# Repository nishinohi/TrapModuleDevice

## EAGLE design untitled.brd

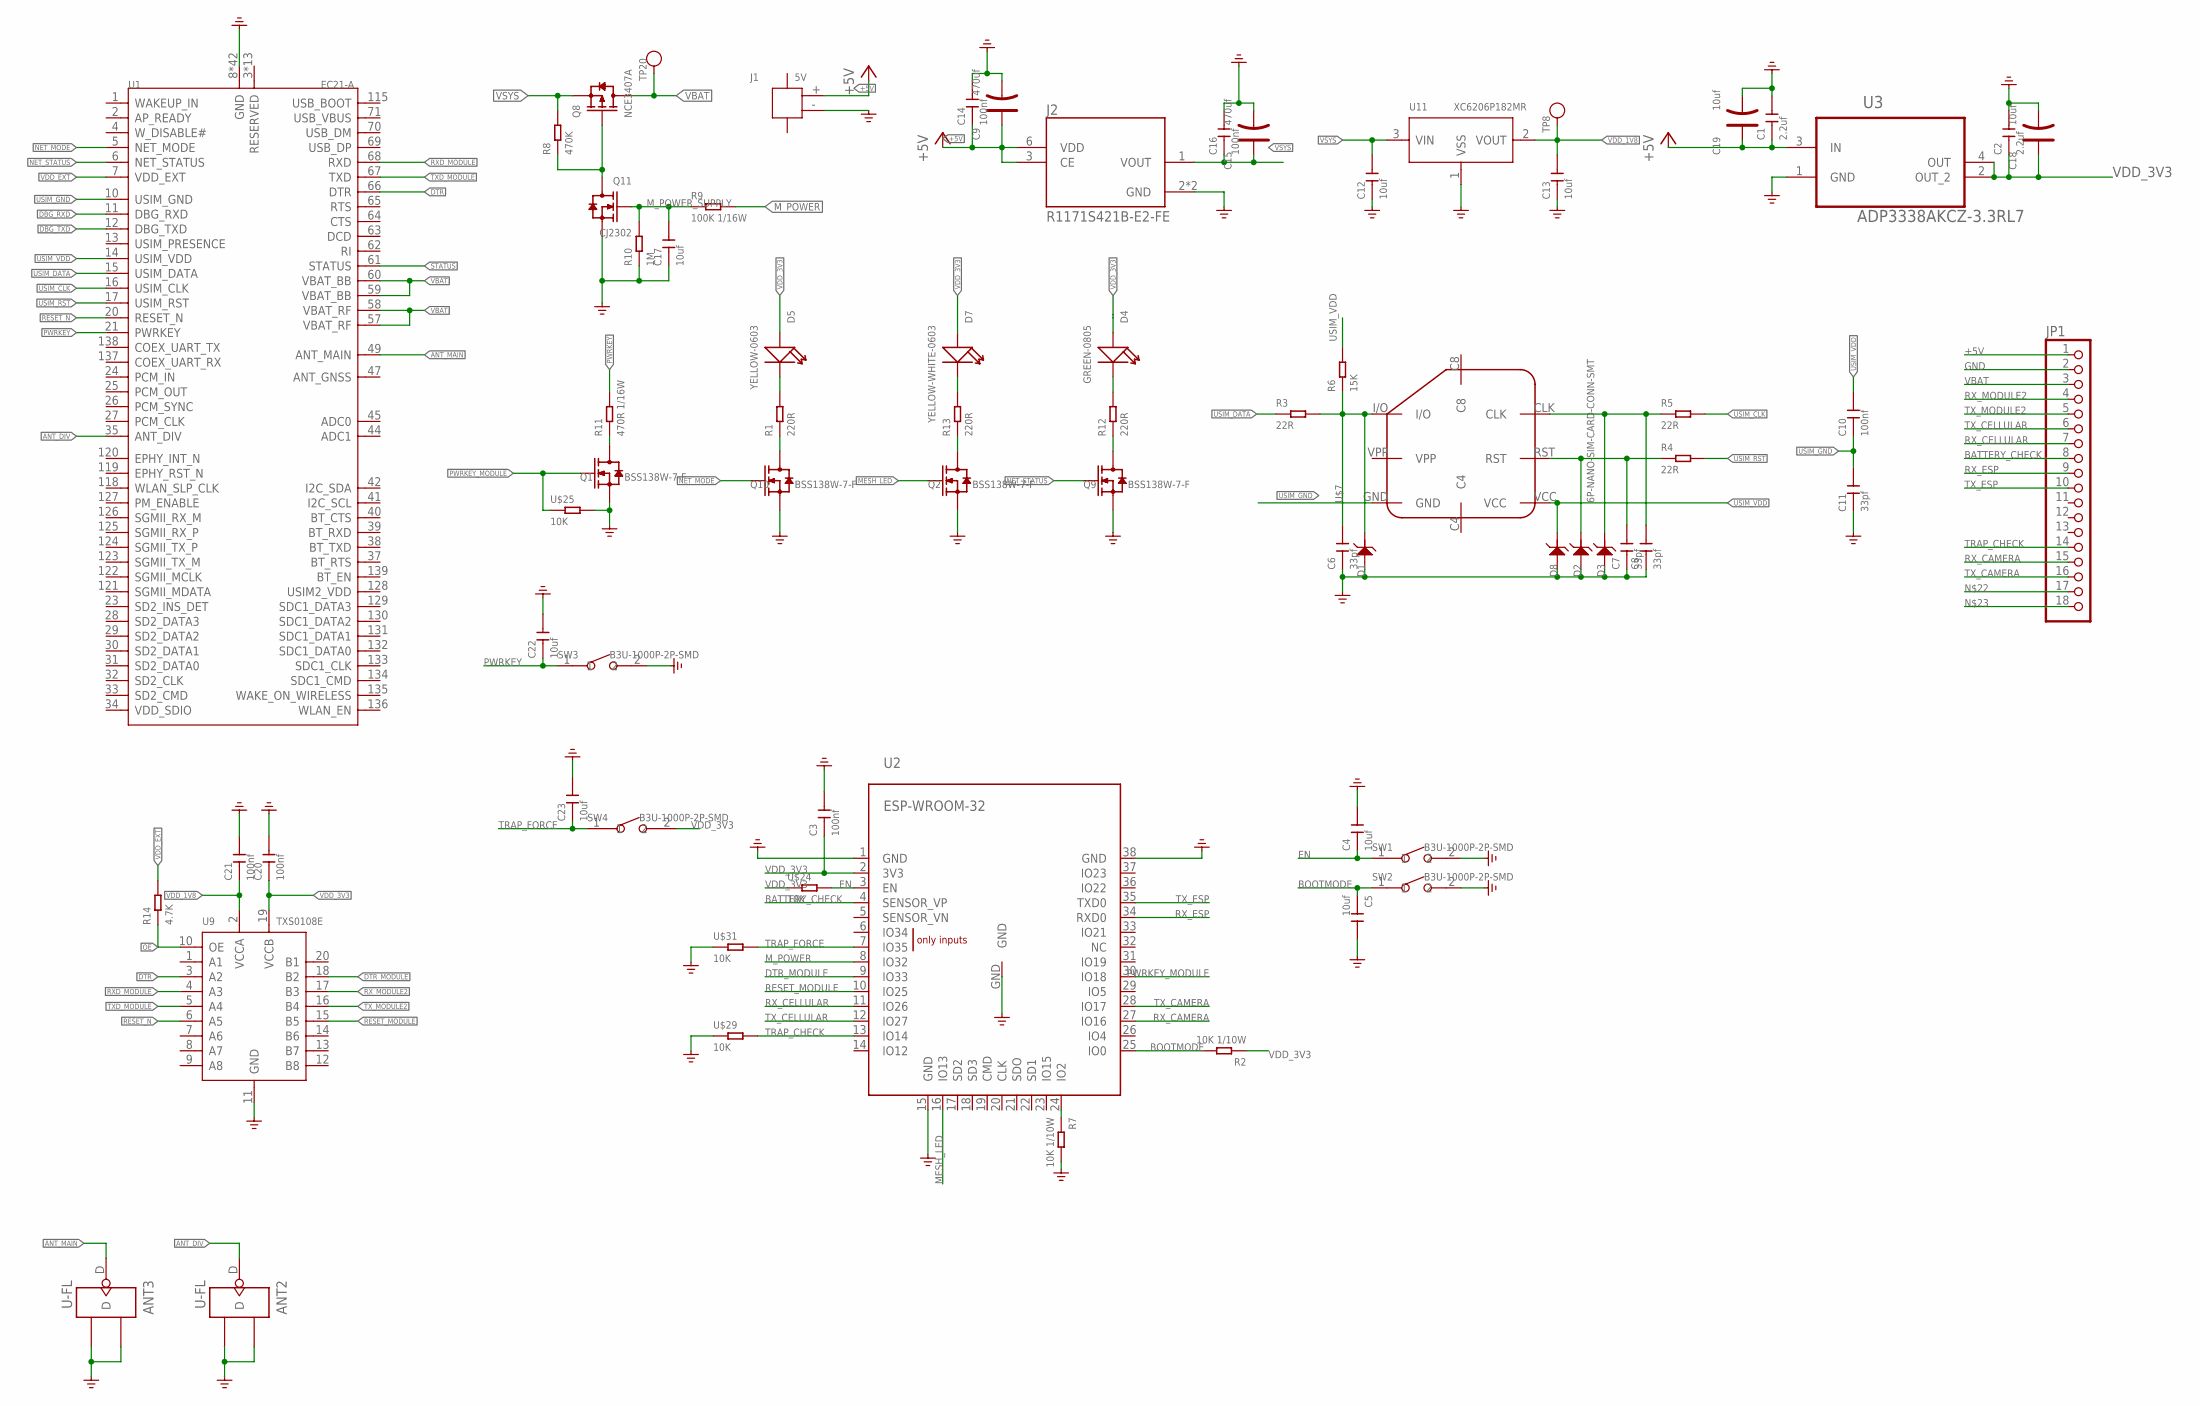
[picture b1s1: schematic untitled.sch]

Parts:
ANT2, ANT3: U-FL; U-FL3P-SMD-2.6X2.6X1.0MM
C1, C2: 2.2uf; C0603
C3, C10, C14, C16, C20, C21: 100nf; C0402
C4, C5, C12, C13, C22, C23: 10uf; C0603
C6, C7, C8, C11: 33pf; C0402
C9, C15: 470uf; AVX-D
C17: 10uf; C0402
C18, C19: 10uf; AVX-A
D1, D2, D3, D8: ESD;DF2S6.8FS; SOD-923
D4: GREEN-0805; LED-0805
D5: YELLOW-0603; LED-0603
D7: YELLOW-WHITE-0603; LED-0603
J1: 5V; HW2-SMD-2.0-90D
J2: R1171S421B-E2-FE; REG_R1171S421B-E2-FE
JP1: HEADER-1X18; 1X18_ROUND70
Q1, Q2, Q9, Q10: BSS138W-7-F; SOT-23
Q8: NCE3407A; SOT-23
Q11: CJ2302; SOT-23
R1, R12, R13: 220R; R0603
R2, R7: 10K 1/10W; R0603
R3, R4, R5: 22R; R0603
R6: 15K; R0603
R8: 470K; R0402
R9: 100K 1/16W; R0402
R10: 1M; R0402
R11: 470R 1/16W; R0402
R14: 4.7K; R0402
SW1, SW2, SW3, SW4: B3U-1000P-2P-SMD; SW2-2.6-3.0X2.5X1.2+0.4MM
TP8, TP20: TEST-POINT'4545'; TP-D45MIL
U1: EC21-A; MODULE144P-1.3-32X29X2.4MM
U2: ESP-WROOM-32
U3: ADP3338AKCZ-3.3RL7; SOT230P700X180-4N
U9: TXS0108E; TSSOP20-0.65-6.5X4.4MM
U11: XC6206P182MR; SOT-23
U$7: 6P-NANO-SIM-CARD-CONN-SMT; 6PIN-NANO-SIM-SMT
U$24, U$25, U$29, U$31: 10K; R0402

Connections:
+5V: C1.1, C9.+, C14.1, C19.+, J1.+ (1), J2.3 (CE), J2.6 (VDD), JP1.1, U3.3 (IN)
ANT_DIV: ANT2.D, U1.35 (ANT_DIV)
ANT_MAIN: ANT3.D, U1.49 (ANT_MAIN)
BATTERY_CHECK: JP1.8, U2.4 (SENSOR_VP)
BOOTMODE: C5.1, R2.2, SW2.1, U2.25 (IO0)
DBG_RXD: U1.11 (DBG_RXD)
DBG_TXD: U1.12 (DBG_TXD)
DTR: U1.66 (DTR), U9.3 (A2)
DTR_MODULE: U2.9 (IO33), U9.18 (B2)
EN: C4.1, SW1.1, U2.3 (EN), U$24.2
GND: ANT2.GND1, ANT2.GND2, ANT3.GND1, ANT3.GND2, C1.2, C2.2, C3.2, C4.2, C5.2, C6.1, C7.1, C8.1, C9.-, C11.1, C12.1, C13.1, C14.2, C15.-, C16.2, C17.1, C18.-, C19.-, C20.2, C21.2, C22.2, C23.2, D1.2 (1), D2.2 (1), D3.2 (1), D8.2 (1), J1.- (2), J2.2 (GND), J2.5 (GND), JP1.2, Q1.2 (S), Q2.2 (S), Q9.2 (S), Q10.2 (S), Q11.2 (S), R7.2, R10.1, SW1.2, SW2.2, SW3.2, U1.8 (GND), U1.9 (GND), U1.19 (GND), U1.22 (GND), U1.36 (GND), U1.46 (GND), U1.48 (GND), U1.50 (GND), U1.51 (GND), U1.52 (GND), U1.53 (GND), U1.54 (GND), U1.56 (GND), U1.72 (GND), U1.85 (GND), U1.86 (GND), U1.87 (GND), U1.88 (GND), U1.89 (GND), U1.90 (GND), U1.91 (GND), U1.92 (GND), U1.93 (GND), U1.94 (GND), U1.95 (GND), U1.96 (GND), U1.97 (GND), U1.98 (GND), U1.99 (GND), U1.100 (GND), U1.101 (GND), U1.102 (GND), U1.103 (GND), U1.104 (GND), U1.105 (GND), U1.106 (GND), U1.107 (GND), U1.108 (GND), U1.109 (GND), U1.110 (GND), U1.111 (GND), U1.112 (GND), U2.1 (GND), U2.15 (GND), U2.38 (GND), U2.GND, U3.1 (GND), U9.11 (GND), U11.1 (VSS), U$25.2, U$29.1, U$31.1
MESH_LED: Q2.1 (G), U2.16 (IO13)
M_POWER: R9.2, U2.8 (IO32)
M_POWER_SUPPLY: C17.2, Q11.1 (G), R9.1, R10.2
unnamed: C8.2, D3.1 (2), R5.1, U$7.CLK
unnamed: C7.2, D2.1 (2), R4.1, U$7.RST
unnamed: Q10.3 (D), R1.1
unnamed: C6.2, D1.1 (2), R3.2, R6.1, U$7.I/O
unnamed: Q1.3 (D), R11.1
unnamed: D5.-, R1.2
unnamed: R7.1, U2.24 (IO2)
unnamed: Q9.3 (D), R12.1
unnamed: D4.-, R12.2
unnamed: Q2.3 (D), R13.1
unnamed: D7.-, R13.2
unnamed: Q8.1 (G), Q11.3 (D), R8.1
NET_MODE: Q10.1 (G), U1.5 (NET_MODE)
NET_STATUS: Q9.1 (G), U1.6 (NET_STATUS)
OE: R14.1, U9.10 (OE)
PWRKEY: C22.1, R11.2, SW3.1, U1.21 (PWRKEY)
PWRKEY_MODULE: Q1.1 (G), U2.30 (IO18), U$25.1
RESET_MODULE: U2.10 (IO25), U9.15 (B5)
RESET_N: U1.20 (RESET_N), U9.6 (A5)
RXD_MODULE: U1.68 (RXD), U9.4 (A3)
RX_CAMERA: JP1.15, U2.27 (IO16)
RX_CELLULAR: JP1.7, U2.11 (IO26)
RX_ESP: JP1.9, U2.34 (RXD0)
RX_MODULE2: JP1.4, U9.17 (B3)
STATUS: U1.61 (STATUS)
TRAP_CHECK: JP1.14, U2.13 (IO14), U$29.2
TRAP_FORCE: C23.1, SW4.1, U2.7 (IO35), U$31.2
TXD_MODULE: U1.67 (TXD), U9.5 (A4)
TX_CAMERA: JP1.16, U2.28 (IO17)
TX_CELLULAR: JP1.6, U2.12 (IO27)
TX_ESP: JP1.10, U2.35 (TXD0)
TX_MODULE2: JP1.5, U9.16 (B4)
USIM_CLK: R5.2, U1.16 (USIM_CLK)
USIM_DATA: R3.1, U1.15 (USIM_DATA)
USIM_GND: C10.1, C11.2, U1.10 (USIM_GND), U$7.GND
USIM_RST: R4.2, U1.17 (USIM_RST)
USIM_VDD: C10.2, D8.1 (2), R6.2, U1.14 (USIM_VDD), U$7.VCC
VBAT: JP1.3, Q8.3 (D), TP20.T, U1.57 (VBAT_RF), U1.58 (VBAT_RF), U1.59 (VBAT_BB), U1.60 (VBAT_BB)
VDD_1V8: C13.2, C21.1, TP8.T, U9.2 (VCCA), U11.2 (VOUT)
VDD_3V3: C2.1, C3.1, C18.+, C20.1, D4.+, D5.+, D7.+, R2.1, SW4.2, U2.2 (3V3), U3.2 (OUT_2), U3.4 (OUT), U9.19 (VCCB), U$24.1
VDD_EXT: R14.2, U1.7 (VDD_EXT)
VSYS: C12.2, C15.+, C16.1, J2.1 (VOUT), Q8.2 (S), R8.2, U11.3 (VIN)

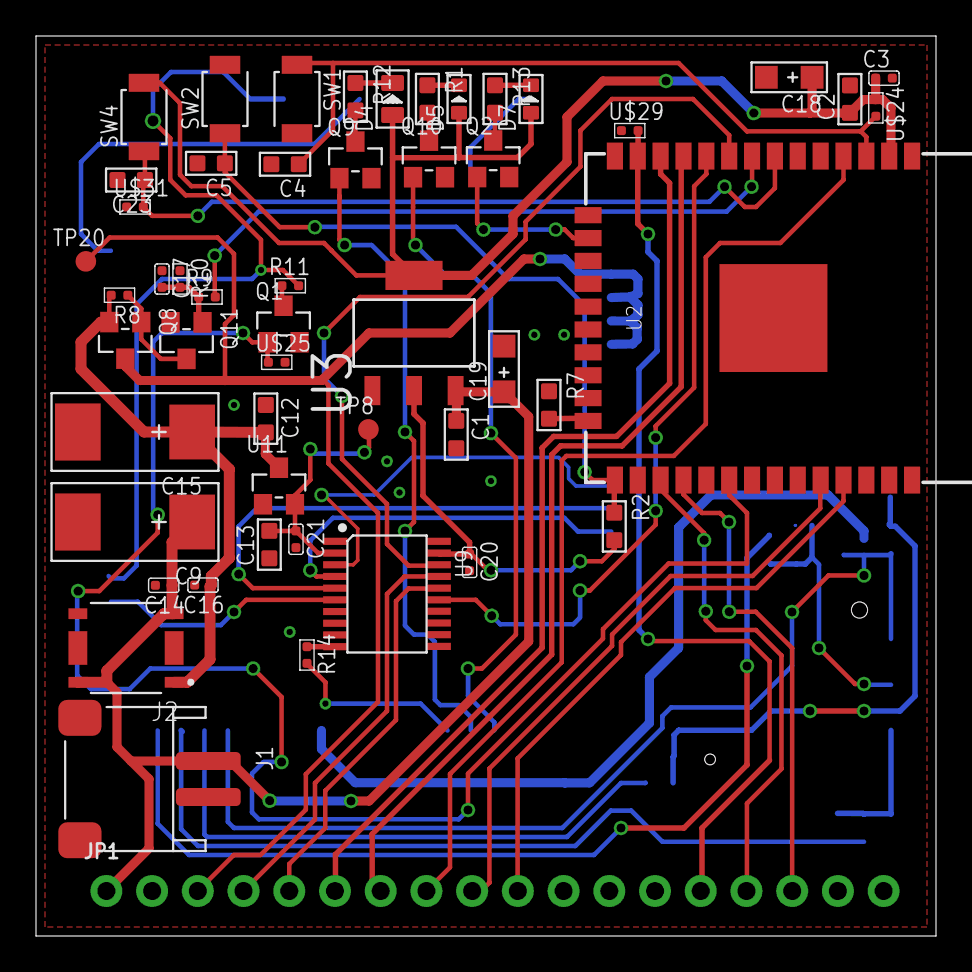
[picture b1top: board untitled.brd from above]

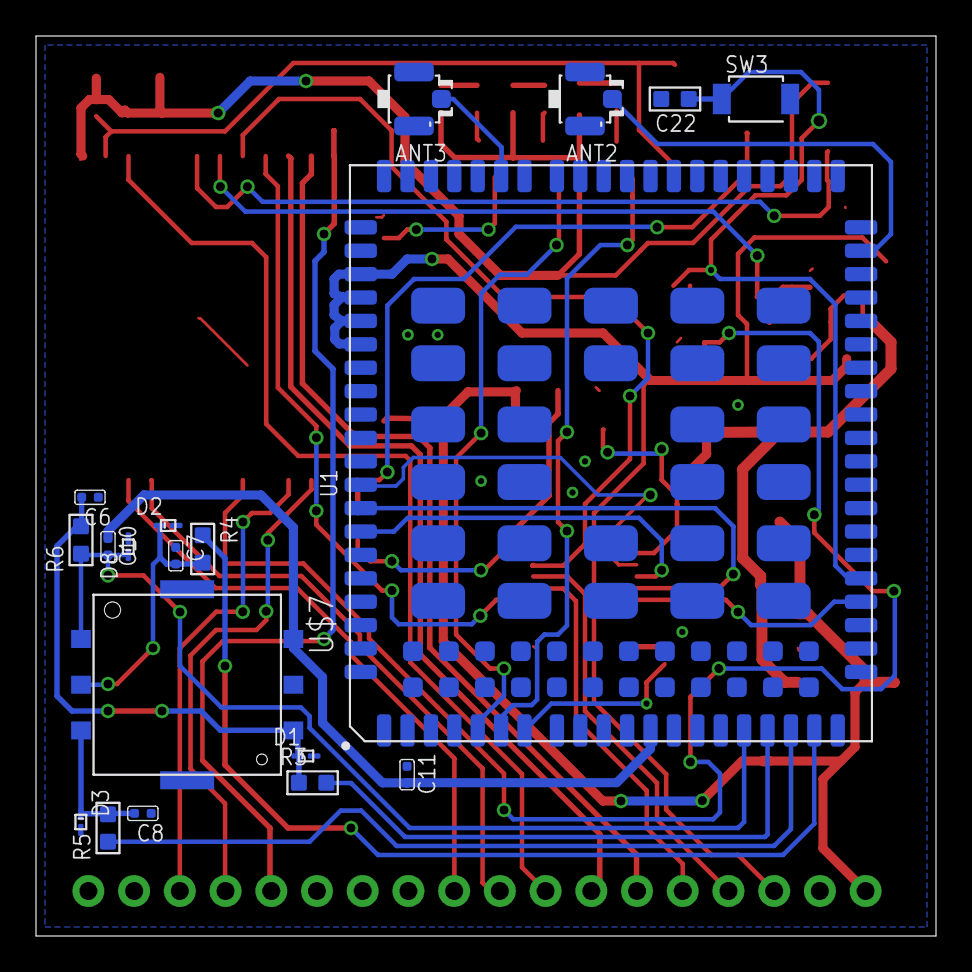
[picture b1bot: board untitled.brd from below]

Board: 2 copper layers, 50.0 x 50.0 mm, 71 parts (19 on the bottom side), 53 nets.

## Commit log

2018-11-29 ver1.0
2018-11-29 MOSをSeeedのものに変更
2018-12-08 発注データ

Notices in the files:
parts and their libraries:
microbuilder: This work is placed in the public domain, and may be freely used for commercial and non-commercial work with the following conditions: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
